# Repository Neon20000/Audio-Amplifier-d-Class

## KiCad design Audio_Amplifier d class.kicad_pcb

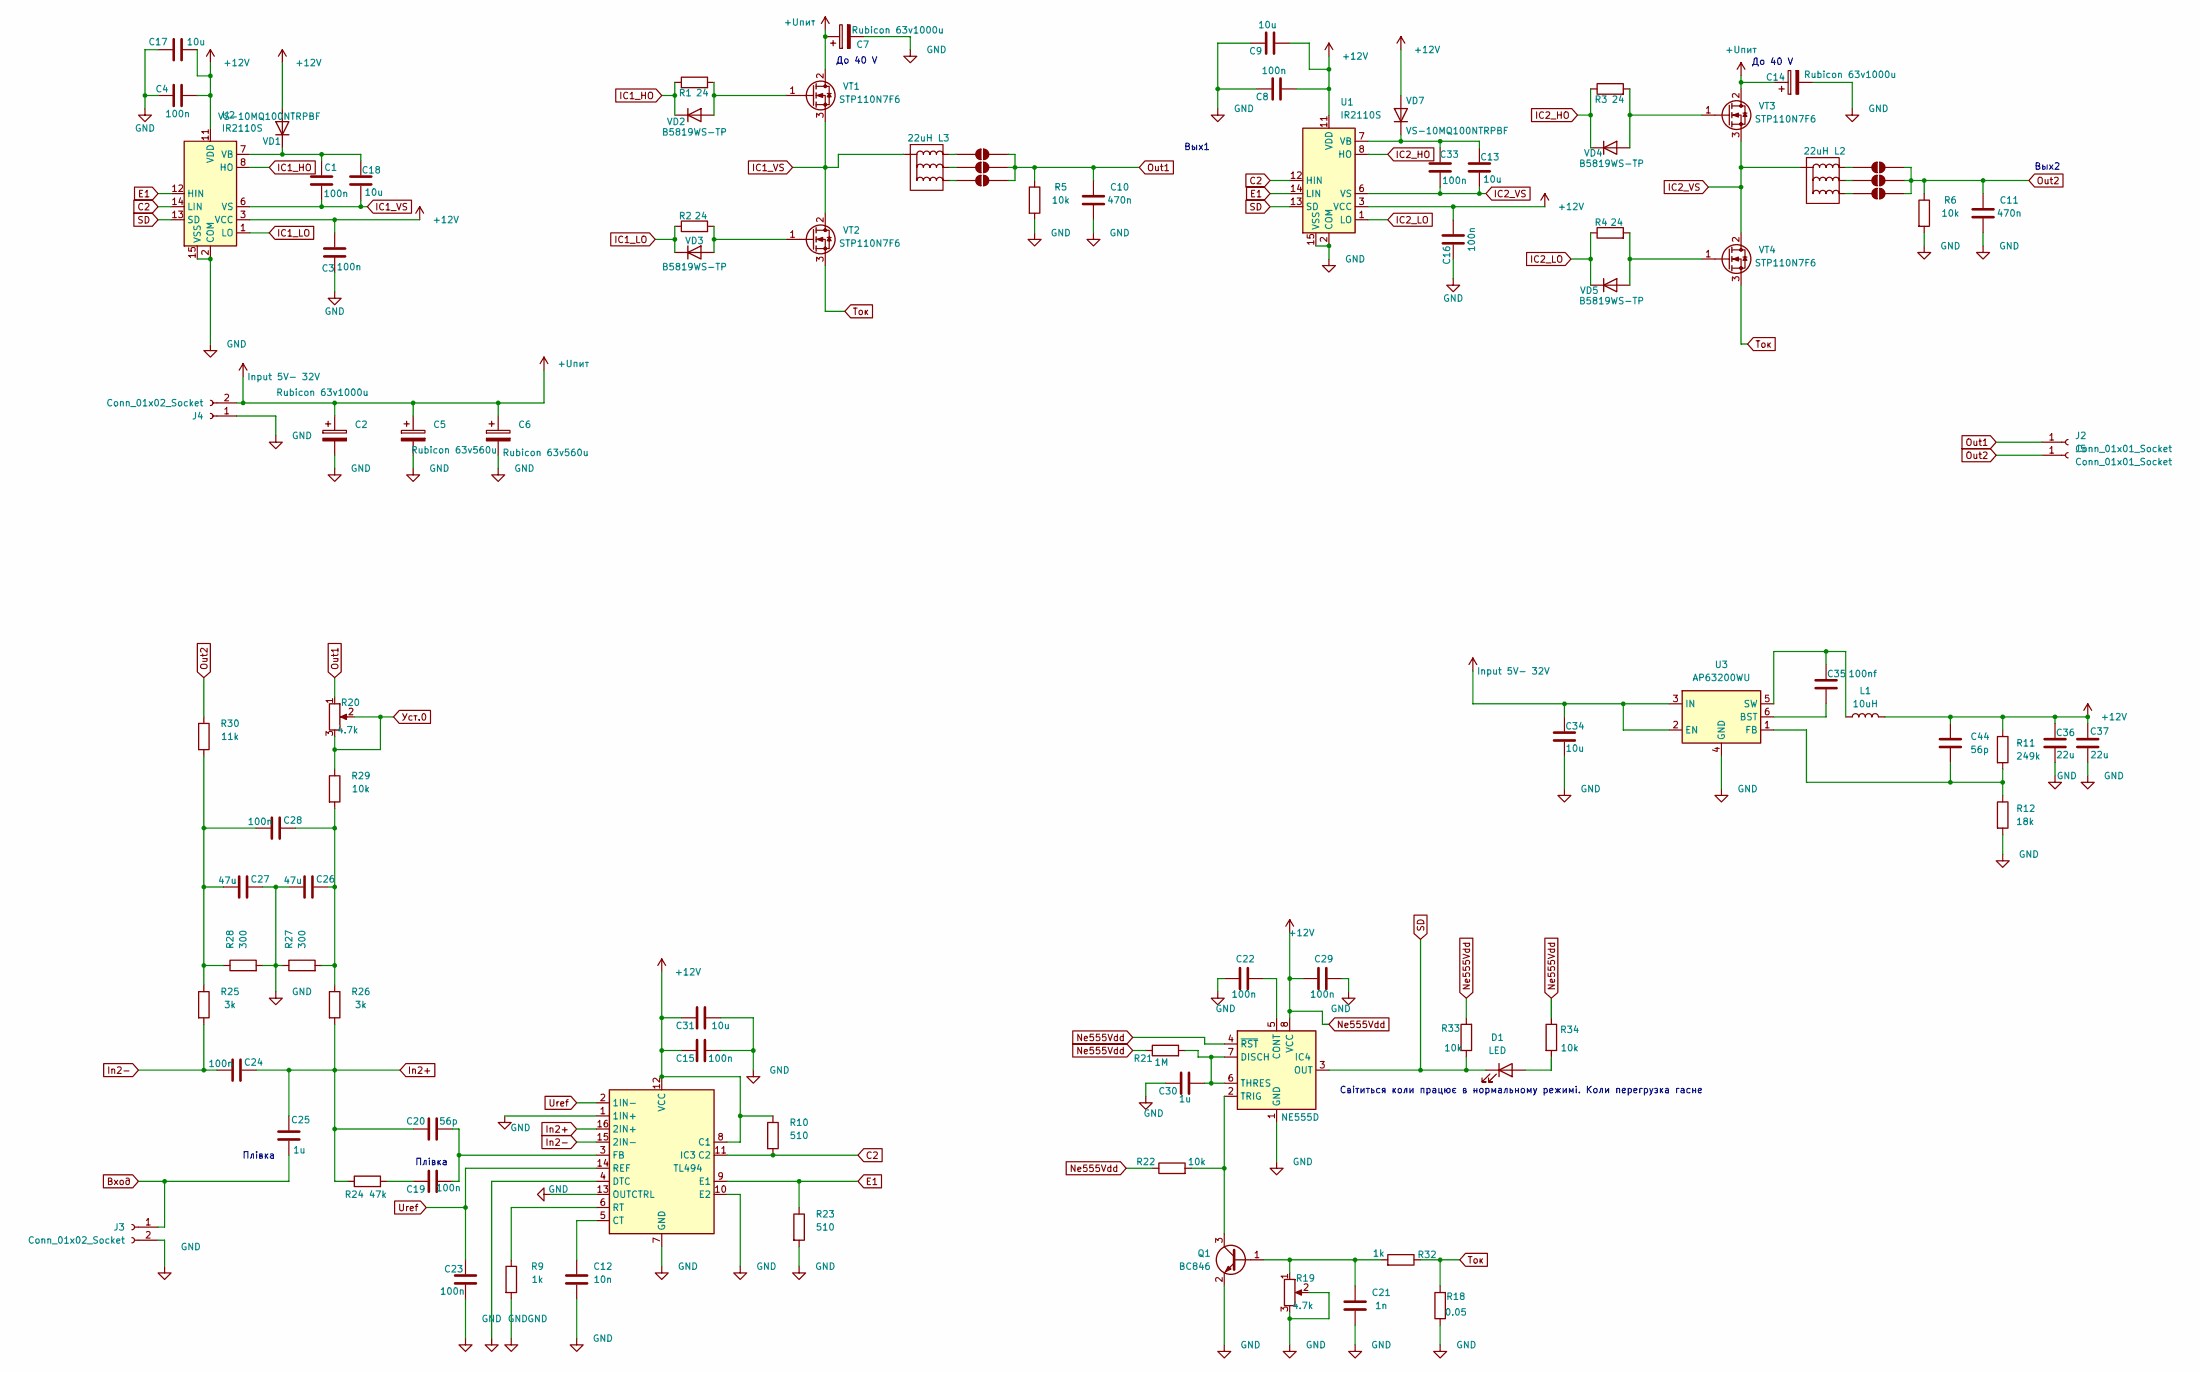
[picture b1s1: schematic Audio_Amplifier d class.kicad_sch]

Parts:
C1, C3, C4, C8, C15, C16, C22, C23, C24, C28, C29, C33: 100n; C_0805_2012Metric_Pad1.18x1.45mm_HandSolder
C2, C7, C14: Rubicon 63v1000u; CP_Radial_D13.0mm_P5.00mm
C5, C6: Rubicon 63v560u; CP_Radial_D13.0mm_P5.00mm
C9, C13, C17, C18: 10u; C_1206_3216Metric_Pad1.33x1.80mm_HandSolder
C10, C11: 470n; C_Rect_L18.0mm_W5.0mm_P15.00mm_FKS3_FKP3
C12: 10n; C_0805_2012Metric_Pad1.18x1.45mm_HandSolder
C19: 100n; C_1206_3216Metric_Pad1.33x1.80mm_HandSolder
C20: 56p; C_0805_2012Metric_Pad1.18x1.45mm_HandSolder
C21: 1n; C_0805_2012Metric_Pad1.18x1.45mm_HandSolder
C25: 1u; C_Rect_L29.0mm_W9.6mm_P27.50mm_MKT
C26, C27: 47u; C_Radial_D5.0mm_H7.0mm_P2.00mm
C30: 1u; C_0805_2012Metric_Pad1.18x1.45mm_HandSolder
C31, C34: 10u; C_0805_2012Metric_Pad1.18x1.45mm_HandSolder
C35: 100nf; C_0603_1608Metric_Pad1.08x0.95mm_HandSolder
C36, C37: 22u; C_1210_3225Metric_Pad1.33x2.70mm_HandSolder
C44: 56p; C_0603_1608Metric_Pad1.08x0.95mm_HandSolder
D1: LED; LED_0603_1608Metric_Pad1.05x0.95mm_HandSolder
IC3: TL494; SO-16_3.9x9.9mm_P1.27mm
IC4: NE555D; SOIC-8_3.9x4.9mm_P1.27mm
J2, J5: Conn_01x01_Socket; MountingHole_2.2mm_M2_Pad_Via
J3: Conn_01x02_Socket; PinHeader_1x02_P2.54mm_Vertical
J4: Conn_01x02_Socket; AMASS_XT30PW-M_1x02_P2.50mm_Horizontal
JP1, JP2, JP3, JP10, JP11, JP12: SolderJumper_2_Open; SolderJumper-2_P1.3mm_Open_RoundedPad1.0x1.5mm
L1: 10uH; L_Bourns-SRU1028_10.0x10.0mm
L2, L3: 22uH; Transformer 3X Обмотка 40мм
Q1: BC846; SOT-23
R1, R2: 24; R_1206_3216Metric
R3, R4: 24; R_1206_3216Metric_Pad1.30x1.75mm_HandSolder
R5: 10k; R_2010_5025Metric
R6: 10k; R_2010_5025Metric_Pad1.40x2.65mm_HandSolder
R9, R32: 1k; R_0805_2012Metric_Pad1.20x1.40mm_HandSolder
R10, R23: 510; R_1206_3216Metric_Pad1.30x1.75mm_HandSolder
R11: 249k; R_0603_1608Metric_Pad0.98x0.95mm_HandSolder
R12: 18k; R_0603_1608Metric_Pad0.98x0.95mm_HandSolder
R18: 0.05; R_2512_6332Metric_Pad1.40x3.35mm_HandSolder
R19, R20: 4.7k; Potentiometer_Bourns_3296W_Vertical
R21: 1M; R_0805_2012Metric_Pad1.20x1.40mm_HandSolder
R22, R29: 10k; R_0805_2012Metric_Pad1.20x1.40mm_HandSolder
R24: 47k; R_0805_2012Metric_Pad1.20x1.40mm_HandSolder
R25, R26: 3k; R_0805_2012Metric_Pad1.20x1.40mm_HandSolder
R27, R28: 300; R_0805_2012Metric_Pad1.20x1.40mm_HandSolder
R30: 11k; R_0805_2012Metric_Pad1.20x1.40mm_HandSolder
R33: 10k; C_0603_1608Metric_Pad1.08x0.95mm_HandSolder
R34: 10k; R_0603_1608Metric_Pad0.98x0.95mm_HandSolder
U1, U2: IR2110S; SOIC-16W_7.5x10.3mm_P1.27mm
U3: AP63200WU; TSOT-23-6
VD1, VD7: VS-10MQ100NTRPBF; D_SMA
VD2, VD3, VD4, VD5: B5819WS-TP; D_SOD-323
VT1, VT2, VT3, VT4: STP110N7F6; TO-220F-3_Vertical

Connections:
+Uпит: C2.1, C5.1, C6.1, C7.1, C14.1, C34.2, J4.2, U3.2 (EN), U3.3 (IN), VT1.2 (D), VT3.2 (D)
C2: IC3.11 (C2), R10.2, U1.12 (HIN), U2.14 (LIN)
E1: IC3.9 (E1), R23.1, U1.14 (LIN), U2.12 (HIN)
GND: C2.2, C3.1, C4.1, C5.2, C6.2, C7.2, C8.2, C9.2, C10.2, C11.2, C12.2, C14.2, C15.2, C16.1, C17.1, C21.2, C22.2, C23.1, C26.2, C27.1, C29.1, C30.1, C31.2, C34.1, C36.1, C37.1, IC3.1 (1IN+), IC3.4 (DTC), IC3.7 (GND), IC3.10 (E2), IC3.13 (OUTCTRL), IC4.1 (GND), J3.2, J4.1, Q1.2 (E), R5.2, R6.2, R9.2, R12.2, R18.1, R19.2, R19.3, R23.2, R27.1, R28.2, U1.2 (COM), U1.15 (VSS), U2.2 (COM), U2.15 (VSS), U3.4 (GND)
IC1_HO: R1.1, U2.8 (HO), VD2.1 (K)
IC1_LO: R2.1, U2.1 (LO), VD3.1 (K)
IC1_VS: C1.2, C18.2, L3.1, U2.6 (VS), VT1.3 (S), VT2.2 (D)
IC2_HO: R3.1, U1.8 (HO), VD4.1 (K)
IC2_LO: R4.1, U1.1 (LO), VD5.1 (K)
IC2_VS: C13.2, C33.2, L2.1, U1.6 (VS), VT3.3 (S), VT4.2 (D)
In2+: C20.1, C24.1, C25.2, IC3.16 (2IN+), R24.1, R26.2
In2-: C24.2, IC3.15 (2IN-), R25.2
Ne555Vdd: C3.2, C4.2, C8.1, C9.1, C15.1, C16.2, C17.2, C29.2, C31.1, C36.2, C37.2, C44.1, IC3.8 (C1), IC3.12 (VCC), IC4.4 (~RST), IC4.8 (VCC), L1.2, R10.1, R11.1, R21.1, R22.1, R33.2, R34.1, U1.3 (VCC), U1.11 (VDD), U2.3 (VCC), U2.11 (VDD), VD1.2 (A), VD7.2 (A)
unnamed: C19.1, R24.2
unnamed: C26.1, C28.1, R26.1, R27.2, R29.2
unnamed: C27.2, C28.2, R25.1, R28.1, R30.2
unnamed: D1.2 (A), R34.2
unnamed: C12.1, IC3.5 (CT)
unnamed: C19.2, C20.2, IC3.3 (FB)
unnamed: IC3.6 (RT), R9.1
unnamed: C22.1, IC4.5 (CONT)
unnamed: C30.2, IC4.6 (THRES), IC4.7 (DISCH), R21.2
unnamed: IC4.2 (TRIG), Q1.3 (C), R22.2
unnamed: JP1.1 (A), L2.2
unnamed: JP2.1 (A), L2.3
unnamed: JP3.1 (A), L2.4
unnamed: JP10.1 (A), L3.2
unnamed: JP11.1 (A), L3.3
unnamed: JP12.1 (A), L3.4
unnamed: C21.1, Q1.1 (B), R19.1, R32.2
unnamed: C13.1, C33.1, U1.7 (VB), VD7.1 (K)
unnamed: C1.1, C18.1, U2.7 (VB), VD1.1 (K)
unnamed: C35.1, U3.6 (BST)
unnamed: C44.2, R11.2, R12.1, U3.1 (FB)
unnamed: C35.2, L1.1, U3.5 (SW)
unnamed: R1.2, VD2.2 (A), VT1.1 (G)
unnamed: R2.2, VD3.2 (A), VT2.1 (G)
unnamed: R3.2, VD4.2 (A), VT3.1 (G)
unnamed: R4.2, VD5.2 (A), VT4.1 (G)
Out1: C10.1, J2.1 (Pin_1_1), JP10.2 (B), JP11.2 (B), JP12.2 (B), R5.1, R20.1
Out2: C11.1, J5.1 (Pin_1_1), JP1.2 (B), JP2.2 (B), JP3.2 (B), R6.1, R30.1
SD: D1.1 (K), IC4.3 (OUT), R33.1, U1.13 (SD), U2.13 (SD)
Uref: C23.2, IC3.2 (1IN-), IC3.14 (REF)
Вход: C25.1, J3.1
Ток: R18.2, R32.1, VT2.3 (S), VT4.3 (S)
Уст.0: R20.2, R20.3, R29.1

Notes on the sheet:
До 40 V
Вых2
Плівка
Світиться коли працює в нормальному режимі. Коли перегрузка гасне
Вых1

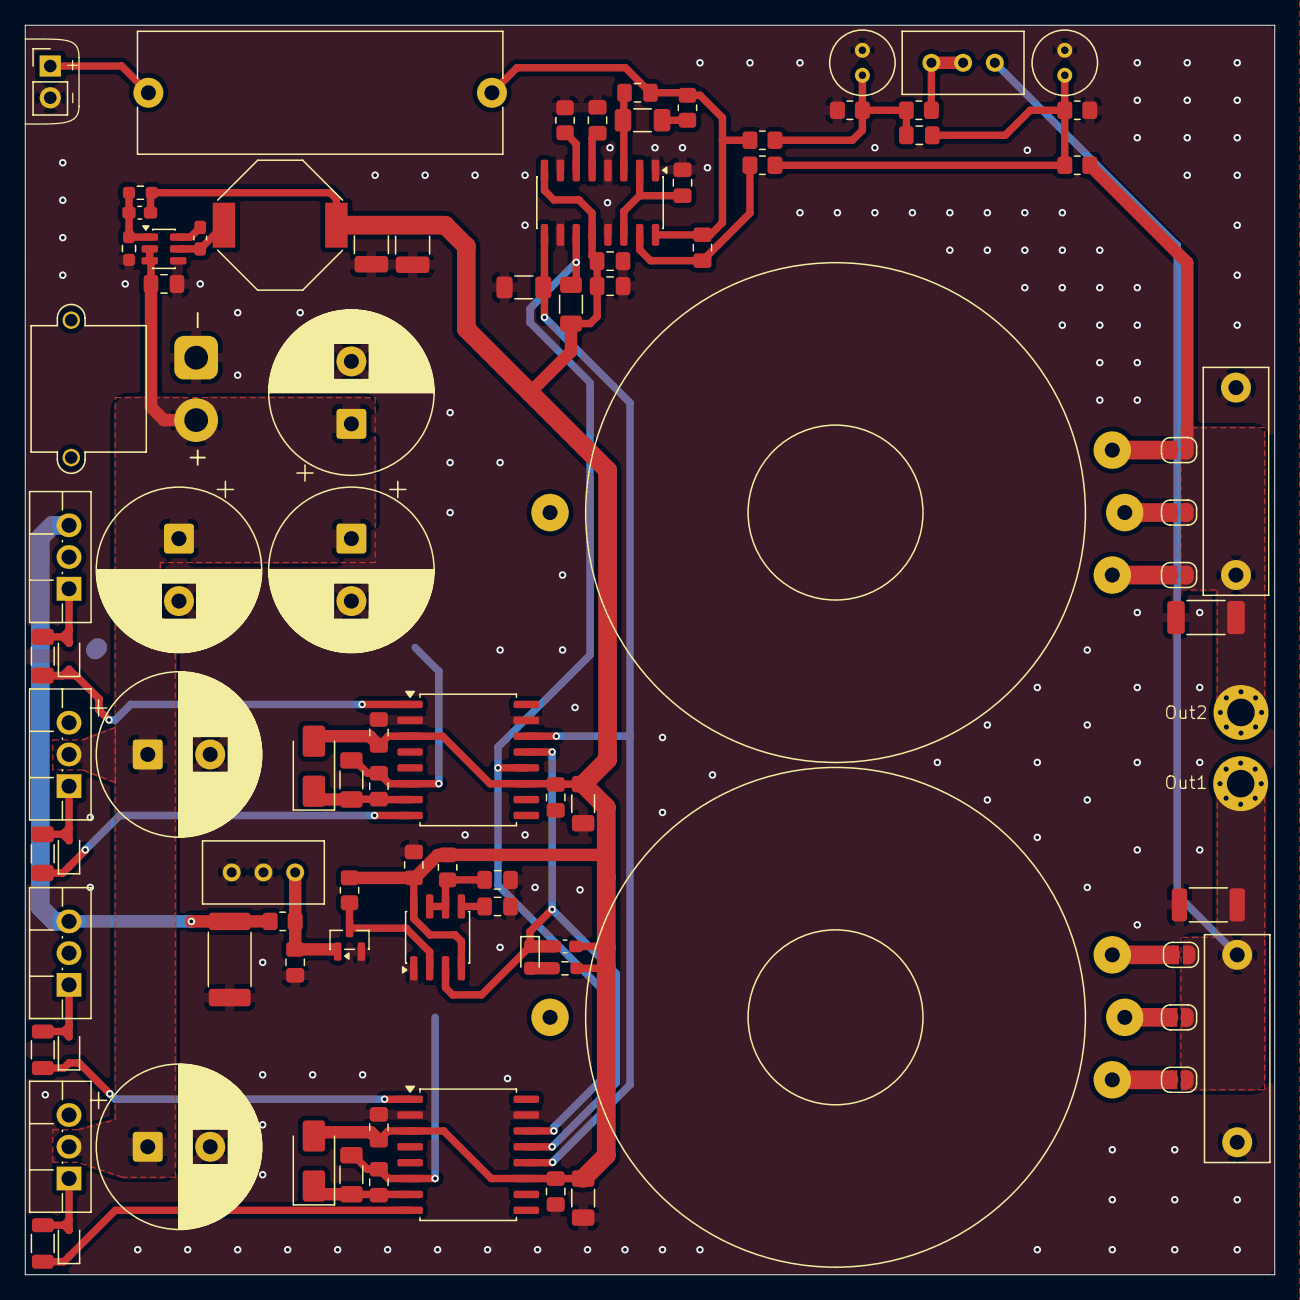
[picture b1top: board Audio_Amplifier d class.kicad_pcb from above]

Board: 2 copper layers, 100.0 x 100.0 mm, 93 parts (0 on the bottom side), 46 nets.
